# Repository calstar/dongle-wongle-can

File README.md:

View this project on [CADLAB.io](https://cadlab.io/project/22833). 

# DongleWongle
A dongle wongle bongle, with a CAN transciver and some proto area.

Layout TBD

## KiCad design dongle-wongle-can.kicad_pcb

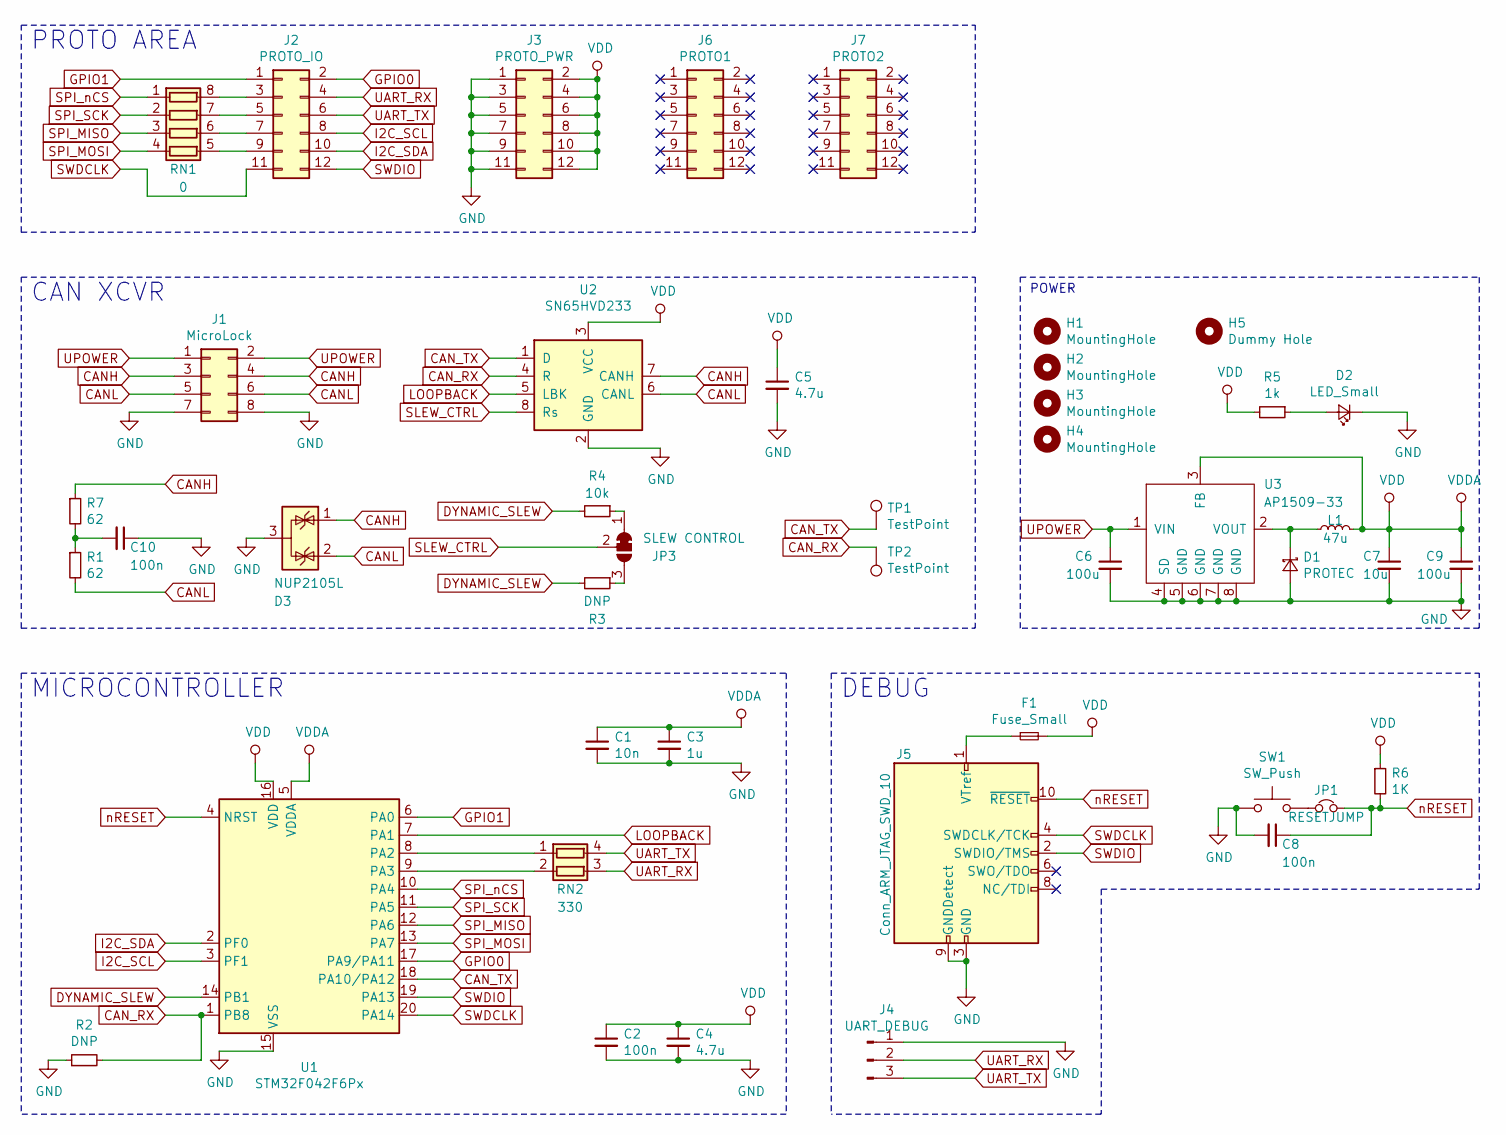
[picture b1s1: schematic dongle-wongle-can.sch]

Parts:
C1: 10n; C_0603_1608Metric
C2, C8, C10: 100n; C_0603_1608Metric
C3: 1u; C_0603_1608Metric
C4, C5: 4.7u; C_0603_1608Metric
C6, C9: 100u; C_1210_3225Metric
C7: 10u; C_0603_1608Metric
D1: PROTEC; D_0603_1608Metric
D2: LED_Small; LED_0603_1608Metric_Castellated
D3: NUP2105L; SOT-23
F1: Fuse_Small; Fuse_0603_1608Metric
H1, H2, H3, H4: MountingHole; MountingHole_3mm
H5: Dummy Hole; airbears
J1: MicroLock; 505448-0871
J2: PROTO_IO; PROTO_2x6
J3: PROTO_PWR; PROTO_2x6
J4: UART_DEBUG; TSM-103-01-L-SV
J5: Conn_ARM_JTAG_SWD_10; FTSH-105-01-L-DV-K
J6: PROTO1; PROTO_2x6
J7: PROTO2; PROTO_2x6
JP1: RESETJUMP; SolderJumper-2_P1.3mm_Bridged_Pad1.0x1.5mm
JP3: SLEW CONTROL; SolderJumper-3_P1.3mm_Bridged2Bar12_Pad1.0x1.5mm
L1: 47u; L_Bourns_SRN6045TA
R1, R7: 62; R_0603_1608Metric
R2, R3: DNP; R_0603_1608Metric
R4: 10k; R_0603_1608Metric
R5: 1k; R_0603_1608Metric
R6: 1K; R_0603_1608Metric
RN1: 0; R_Array_Convex_4x1206
RN2: 330; R_Array_Convex_2x0606
SW1: SW_Push; SW_SPST_CK_RS282G05A3
TP1, TP2: TestPoint; TestPoint_Pad_1.0x1.0mm
U1: STM32F042F6Px; TSSOP-20_4.4x6.5mm_P0.65mm
U2: SN65HVD233; SOIC-8_3.9x4.9mm_P1.27mm
U3: AP1509-33; SOIC-8_3.9x4.9mm_P1.27mm

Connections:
CANH: D3.1 (K), J1.3, J1.4, R7.1, U2.7 (CANH)
CANL: D3.2 (K), J1.5, J1.6, R1.2, U2.6 (CANL)
CAN_RX: R2.2, TP2.1, U1.1 (PB8), U2.4 (R)
CAN_TX: TP1.1, U1.18 (PA10/PA12), U2.1 (D)
DYNAMIC_SLEW: R3.2, R4.2, U1.14 (PB1)
GND: C1.2, C2.2, C3.2, C4.2, C5.2, C6.2, C7.2, C8.2, C9.2, C10.1, D1.2 (A), D2.1 (K), D3.3 (A), J1.7, J1.8, J3.1, J3.3, J3.5, J3.7, J3.9, J3.11, J4.1, J5.3 (GND), J5.5 (GND), J5.9 (GNDDetect), R2.1, SW1.1, U1.15 (VSS), U2.2 (GND), U3.4 (SD), U3.5 (GND), U3.6 (GND), U3.7 (GND), U3.8 (GND)
GPIO0: J2.2, U1.17 (PA9/PA11)
GPIO1: J2.1, U1.6 (PA0)
I2C_SCL: J2.8, U1.3 (PF1)
I2C_SDA: J2.10, U1.2 (PF0)
LOOPBACK: U1.7 (PA1), U2.5 (LBK)
unnamed: C10.2, R1.1, R7.2
unnamed: D1.1 (K), L1.1, U3.2 (VOUT)
unnamed: D2.2 (A), R5.1
unnamed: F1.1, J5.1 (VTref)
unnamed: J2.3, RN1.8 (R1.2)
unnamed: J2.5, RN1.7 (R2.2)
unnamed: J2.7, RN1.6 (R3.2)
unnamed: J2.9, RN1.5 (R4.2)
unnamed: JP1.1, SW1.2
unnamed: JP3.1 (A), R4.1
unnamed: JP3.3 (B), R3.1
unnamed: RN2.1 (R1.1), U1.8 (PA2)
unnamed: RN2.2 (R2.1), U1.9 (PA3)
SLEW_CTRL: JP3.2 (C), U2.8 (Rs)
SPI_MISO: RN1.3 (R3.1), U1.12 (PA6)
SPI_MOSI: RN1.4 (R4.1), U1.13 (PA7)
SPI_SCK: RN1.2 (R2.1), U1.11 (PA5)
SPI_nCS: RN1.1 (R1.1), U1.10 (PA4)
SWDCLK: J2.11, J5.4 (SWDCLK/TCK), U1.20 (PA14)
SWDIO: J2.12, J5.2 (SWDIO/TMS), U1.19 (PA13)
UART_RX: J2.4, J4.2, RN2.3 (R2.2)
UART_TX: J2.6, J4.3, RN2.4 (R1.2)
UPOWER: C6.1, J1.1, J1.2, U3.1 (VIN)
VDD: C1.1, C2.1, C3.1, C4.1, C5.1, C7.1, C9.1, F1.2, J3.2, J3.4, J3.6, J3.8, J3.10, J3.12, L1.2, R5.2, R6.1, U1.5 (VDDA), U1.16 (VDD), U2.3 (VCC), U3.3 (FB)
nRESET: C8.1, J5.10 (~RESET~), JP1.2, R6.2, U1.4 (NRST)

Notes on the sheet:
MICROCONTROLLER
PROTO AREA
CAN XCVR
DEBUG
POWER

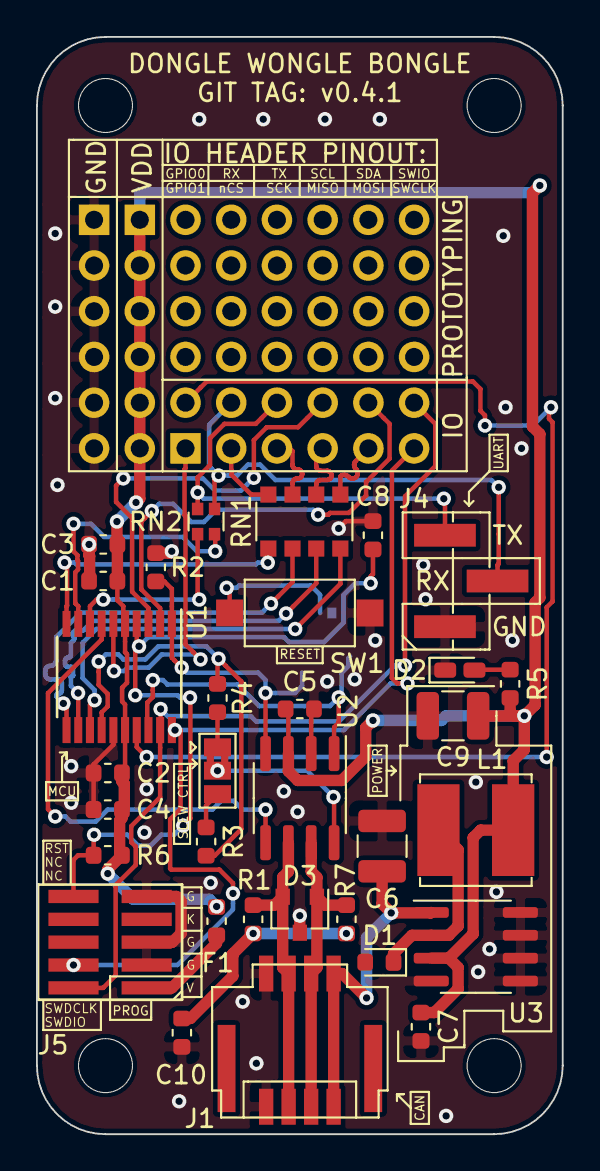
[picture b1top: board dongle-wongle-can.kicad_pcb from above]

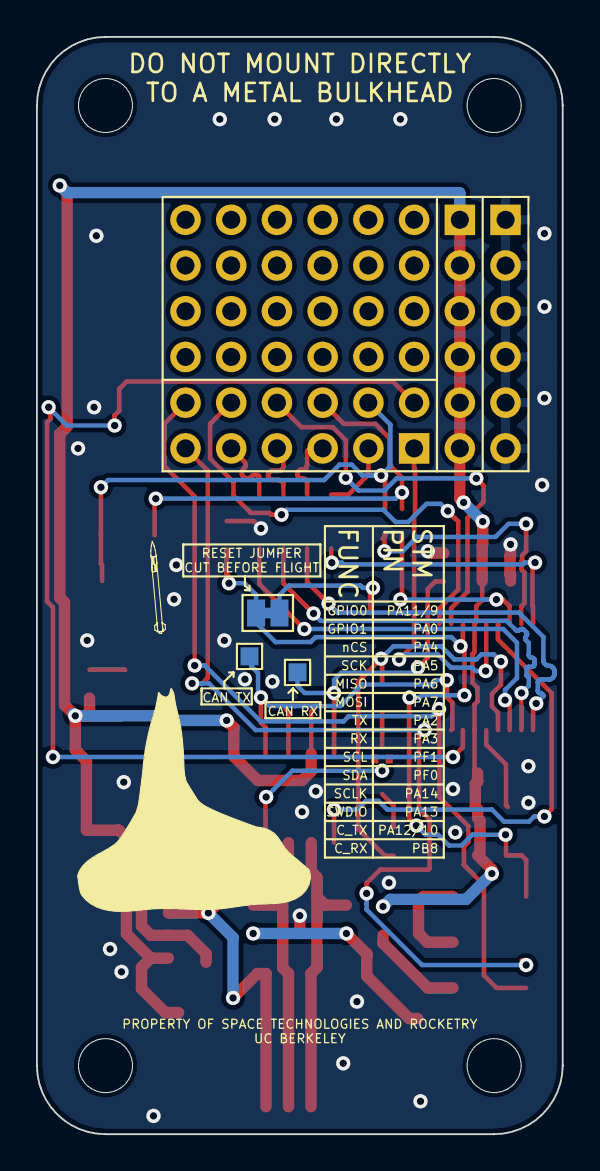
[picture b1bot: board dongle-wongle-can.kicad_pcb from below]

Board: 2 copper layers, 29.2 x 61.0 mm, 44 parts (4 on the bottom side), 36 nets.

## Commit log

2020-04-26 Initial Schematic work (hopefully everything but power)
2020-04-26 add power
2020-04-26 add gitignore
2020-04-26 updated project layout
2020-04-26 updated footprints
2020-04-26 Backlink to CADLAB.io has been added.
2020-04-26 add layout
2020-04-26 improve silk
2020-04-27 make silk 10/10 and add some art
2020-04-27 forgot to refill zones, like a dumbass
2020-04-27 increase edge cuts to make osh happy
2020-04-27 stitch grounds a bit
2020-04-27 change resistor pack footprints
2020-04-27 fix stupid fields
2020-04-29 implement suggested changes
2020-04-29 fix some bom thingies
2020-05-04 implemented some changes
2020-05-04 moved some vias off of pads
2020-05-04 added protection diode, and fixed jason's OCD
2020-05-05 add tp (expensive) on tx and rx
